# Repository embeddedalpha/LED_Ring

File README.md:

# LED_Ring
Just a normal LED Ring

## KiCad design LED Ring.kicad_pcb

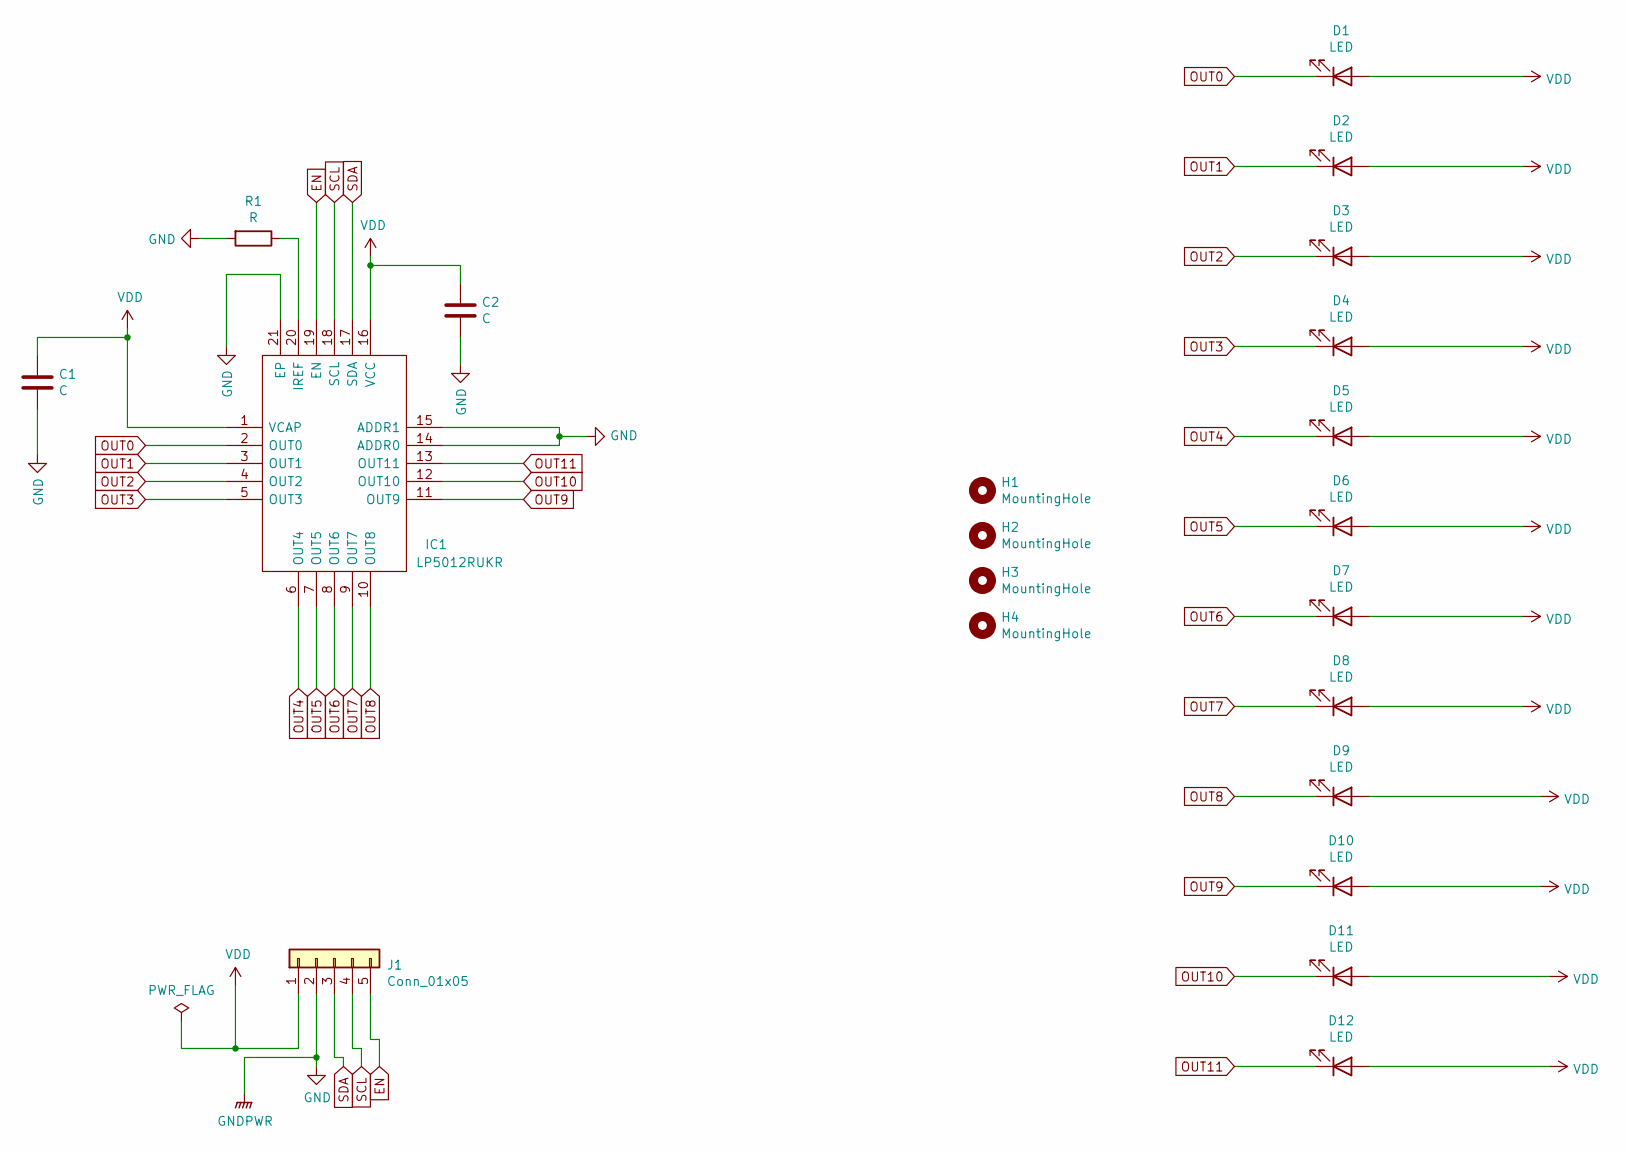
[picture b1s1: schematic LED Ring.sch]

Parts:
C1, C2: C; CP_Elec_3x5.4
D1, D2, D3, D4, D5, D6, D7, D8, D9, D10, D11, D12: LED; LED_0603_1608Metric
H1, H2, H3, H4: MountingHole; MountingHole_3.2mm_M3_DIN965_Pad
IC1: LP5012RUKR; QFN40P300X300X80-21N-D; Mouser Part Number 595-LP5012RUKR
J1: Conn_01x05; PinSocket_1x05_P2.54mm_Horizontal
R1: R; R_0402_1005Metric

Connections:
EN: IC1.19 (EN), J1.5
GND: C1.2, C2.2, IC1.14 (ADDR0), IC1.15 (ADDR1), IC1.21 (EP), J1.2, R1.2
unnamed: IC1.20 (IREF), R1.1
OUT0: D1.1 (K), IC1.2 (OUT0)
OUT1: D2.1 (K), IC1.3 (OUT1)
OUT2: D3.1 (K), IC1.4 (OUT2)
OUT3: D4.1 (K), IC1.5 (OUT3)
OUT4: D5.1 (K), IC1.6 (OUT4)
OUT5: D6.1 (K), IC1.7 (OUT5)
OUT6: D7.1 (K), IC1.8 (OUT6)
OUT7: D8.1 (K), IC1.9 (OUT7)
OUT8: D9.1 (K), IC1.10 (OUT8)
OUT9: D10.1 (K), IC1.11 (OUT9)
OUT10: D11.1 (K), IC1.12 (OUT10)
OUT11: D12.1 (K), IC1.13 (OUT11)
SCL: IC1.18 (SCL), J1.4
SDA: IC1.17 (SDA), J1.3
VDD: C1.1, C2.1, D1.2 (A), D2.2 (A), D3.2 (A), D4.2 (A), D5.2 (A), D6.2 (A), D7.2 (A), D8.2 (A), D9.2 (A), D10.2 (A), D11.2 (A), D12.2 (A), IC1.1 (VCAP), IC1.16 (VCC), J1.1

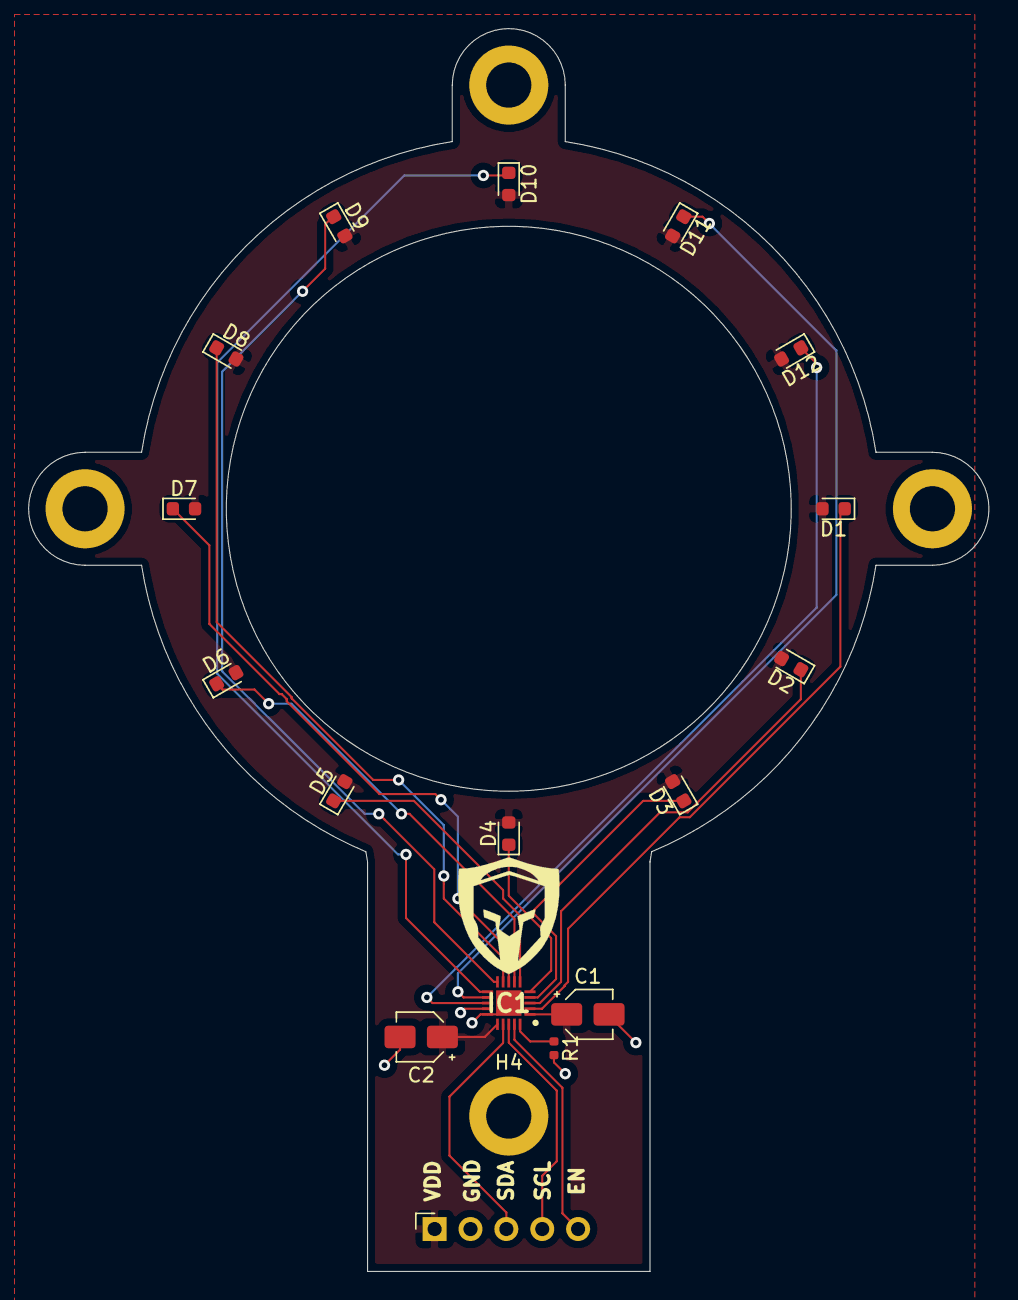
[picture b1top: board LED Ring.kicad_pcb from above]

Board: 2 copper layers, 68.0 x 88.0 mm, 21 parts (0 on the bottom side), 18 nets.
